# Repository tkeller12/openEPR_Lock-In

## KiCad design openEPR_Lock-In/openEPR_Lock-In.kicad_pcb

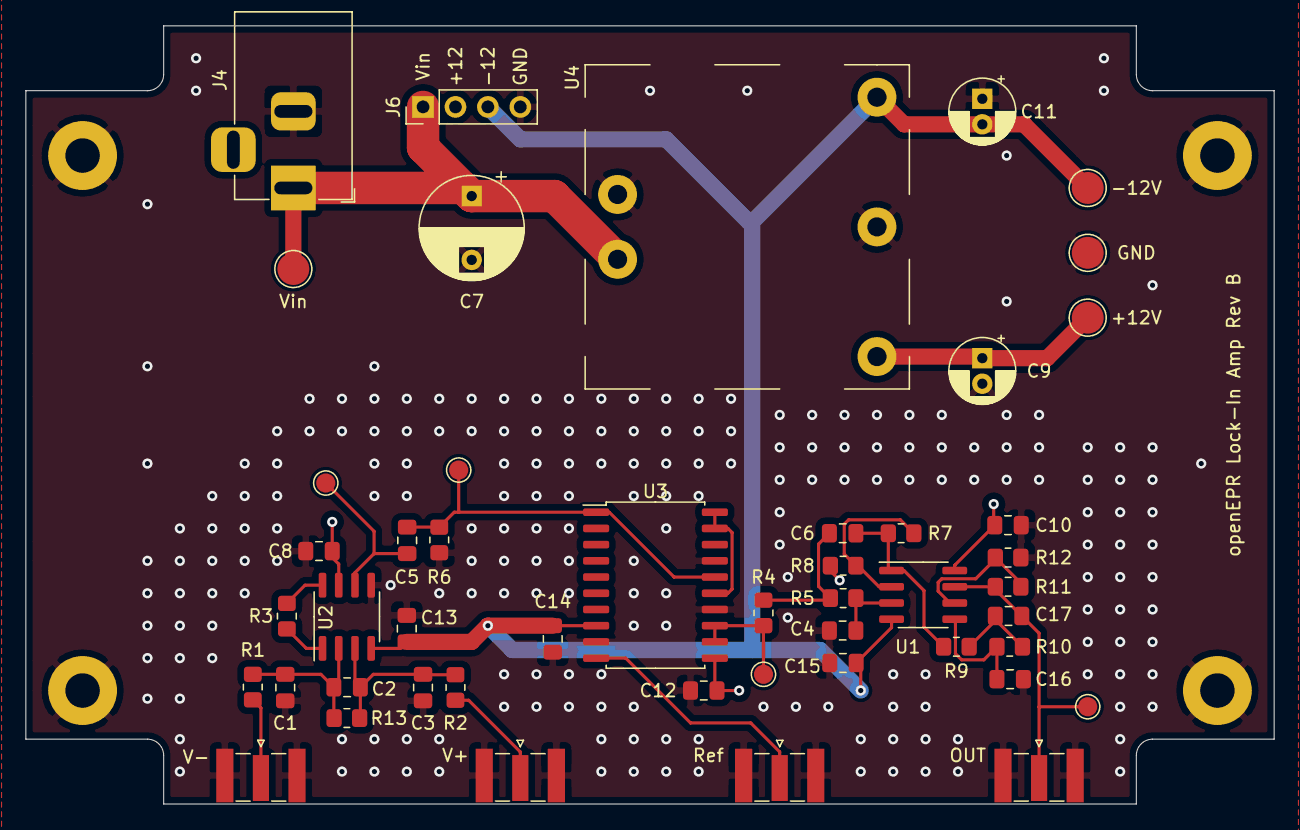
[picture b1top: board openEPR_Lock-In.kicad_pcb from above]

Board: 4 copper layers, 97.8 x 61.0 mm, 52 parts (0 on the bottom side), 23 nets.

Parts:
C1, C3, C5, C8, C10, C12, C13, C14, C15: 100nF; C_0805_2012Metric_Pad1.18x1.45mm_HandSolder
C2: C_Small; C_0805_2012Metric_Pad1.18x1.45mm_HandSolder
C4, C6, C16, C17: 10nF; C_0805_2012Metric_Pad1.18x1.45mm_HandSolder
C7: CP_Small; CP_Radial_D8.0mm_P5.00mm
C9, C11: CP_Small; CP_Radial_D5.0mm_P2.00mm
H1, H2, H3, H4: MountingHole_Pad; MountingHole_2.7mm_M2.5_Pad
J1: Signal+; SMA_Samtec_SMA-J-P-X-ST-EM1_EdgeMount
J2: Signal-; SMA_Samtec_SMA-J-P-X-ST-EM1_EdgeMount
J3: Output; SMA_Samtec_SMA-J-P-X-ST-EM1_EdgeMount
J4: Barrel_Jack_Switch; BarrelJack_Horizontal
J5: REF; SMA_Samtec_SMA-J-P-X-ST-EM1_EdgeMount
J6: Conn_01x04_Male; PinHeader_1x04_P2.54mm_Vertical
R1, R2: 10; R_0805_2012Metric_Pad1.20x1.40mm_HandSolder
R3: 50; R_0805_2012Metric_Pad1.20x1.40mm_HandSolder
R4, R5: 267k; R_0805_2012Metric_Pad1.20x1.40mm_HandSolder
R6, R8, R12: 10k; R_0805_2012Metric_Pad1.20x1.40mm_HandSolder
R7: 5.76k; R_0805_2012Metric_Pad1.20x1.40mm_HandSolder
R9, R10: 154k; R_0805_2012Metric_Pad1.20x1.40mm_HandSolder
R11: 16.5k; R_0805_2012Metric_Pad1.20x1.40mm_HandSolder
R13: 1M; R_0805_2012Metric_Pad1.20x1.40mm_HandSolder
TP1, TP2, TP3, TP4: TestPoint; TestPoint_Pad_D2.5mm
TP5, TP6, TP7, TP8: TestPoint; TestPoint_Pad_D1.5mm
U1: OP2177; SOIC-8_3.9x4.9mm_P1.27mm
U2: AD620; SOIC-8_3.9x4.9mm_P1.27mm
U3: AD630ARZ; SOIC-20W_7.5x12.8mm_P1.27mm
U4: PQDE6W-D

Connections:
/DEMOD: R4.2, TP8.1, U3.12, U3.13
/IN-AMP_FILTERED: C5.1, R6.2, TP6.1, U3.1, U3.16
/IN-AMP_OUT: C5.2, TP5.1, U2.6
/INPUT+: J1.1, R2.2
/INPUT-: J2.1, R1.2
/OUTPUT: C17.1, J3.1, R11.2, TP7.1, U1.7
/REF: J5.1, U3.10
/V+: C8.1, C9.1, C10.1, C12.1, J6.2, TP3.1, U1.8, U2.7, U3.11, U4.3
/V-: C11.2, C13.1, C14.1, C15.1, J6.3, TP4.1, U1.4, U2.4, U3.8, U4.5
/Vin: C7.1, J4.1, J6.1, TP2.1, U4.2
GND: C1.2, C3.1, C4.2, C7.2, C8.2, C9.2, C10.2, C11.1, C12.2, C13.2, C14.2, C15.2, C16.2, H1.1, H2.1, H3.1, H4.1, J1.2, J2.2, J3.2, J4.2, J5.2, J6.4, R6.1, R8.1, R12.1, TP1.1, U2.5, U3.9, U3.14, U3.17, U4.1, U4.4
unnamed: C1.1, C2.2, R1.1, R13.2, U2.2
unnamed: C2.1, C3.2, R2.1, R13.1, U2.3
unnamed: C4.1, R5.1, U1.3
unnamed: C6.1, R7.2, R9.1, U1.1
unnamed: C6.2, R4.1, R5.2
unnamed: C16.1, R10.2, U1.5
unnamed: C17.2, R9.2, R10.1
unnamed: R3.1, U2.8
unnamed: R3.2, U2.1
unnamed: R7.1, R8.2, U1.2
unnamed: R11.1, R12.2, U1.6
unnamed: U3.15, U3.19, U3.20

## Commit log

2025-05-05 Adding KiCAD files
2025-05-09 Updating to latest kicad version
